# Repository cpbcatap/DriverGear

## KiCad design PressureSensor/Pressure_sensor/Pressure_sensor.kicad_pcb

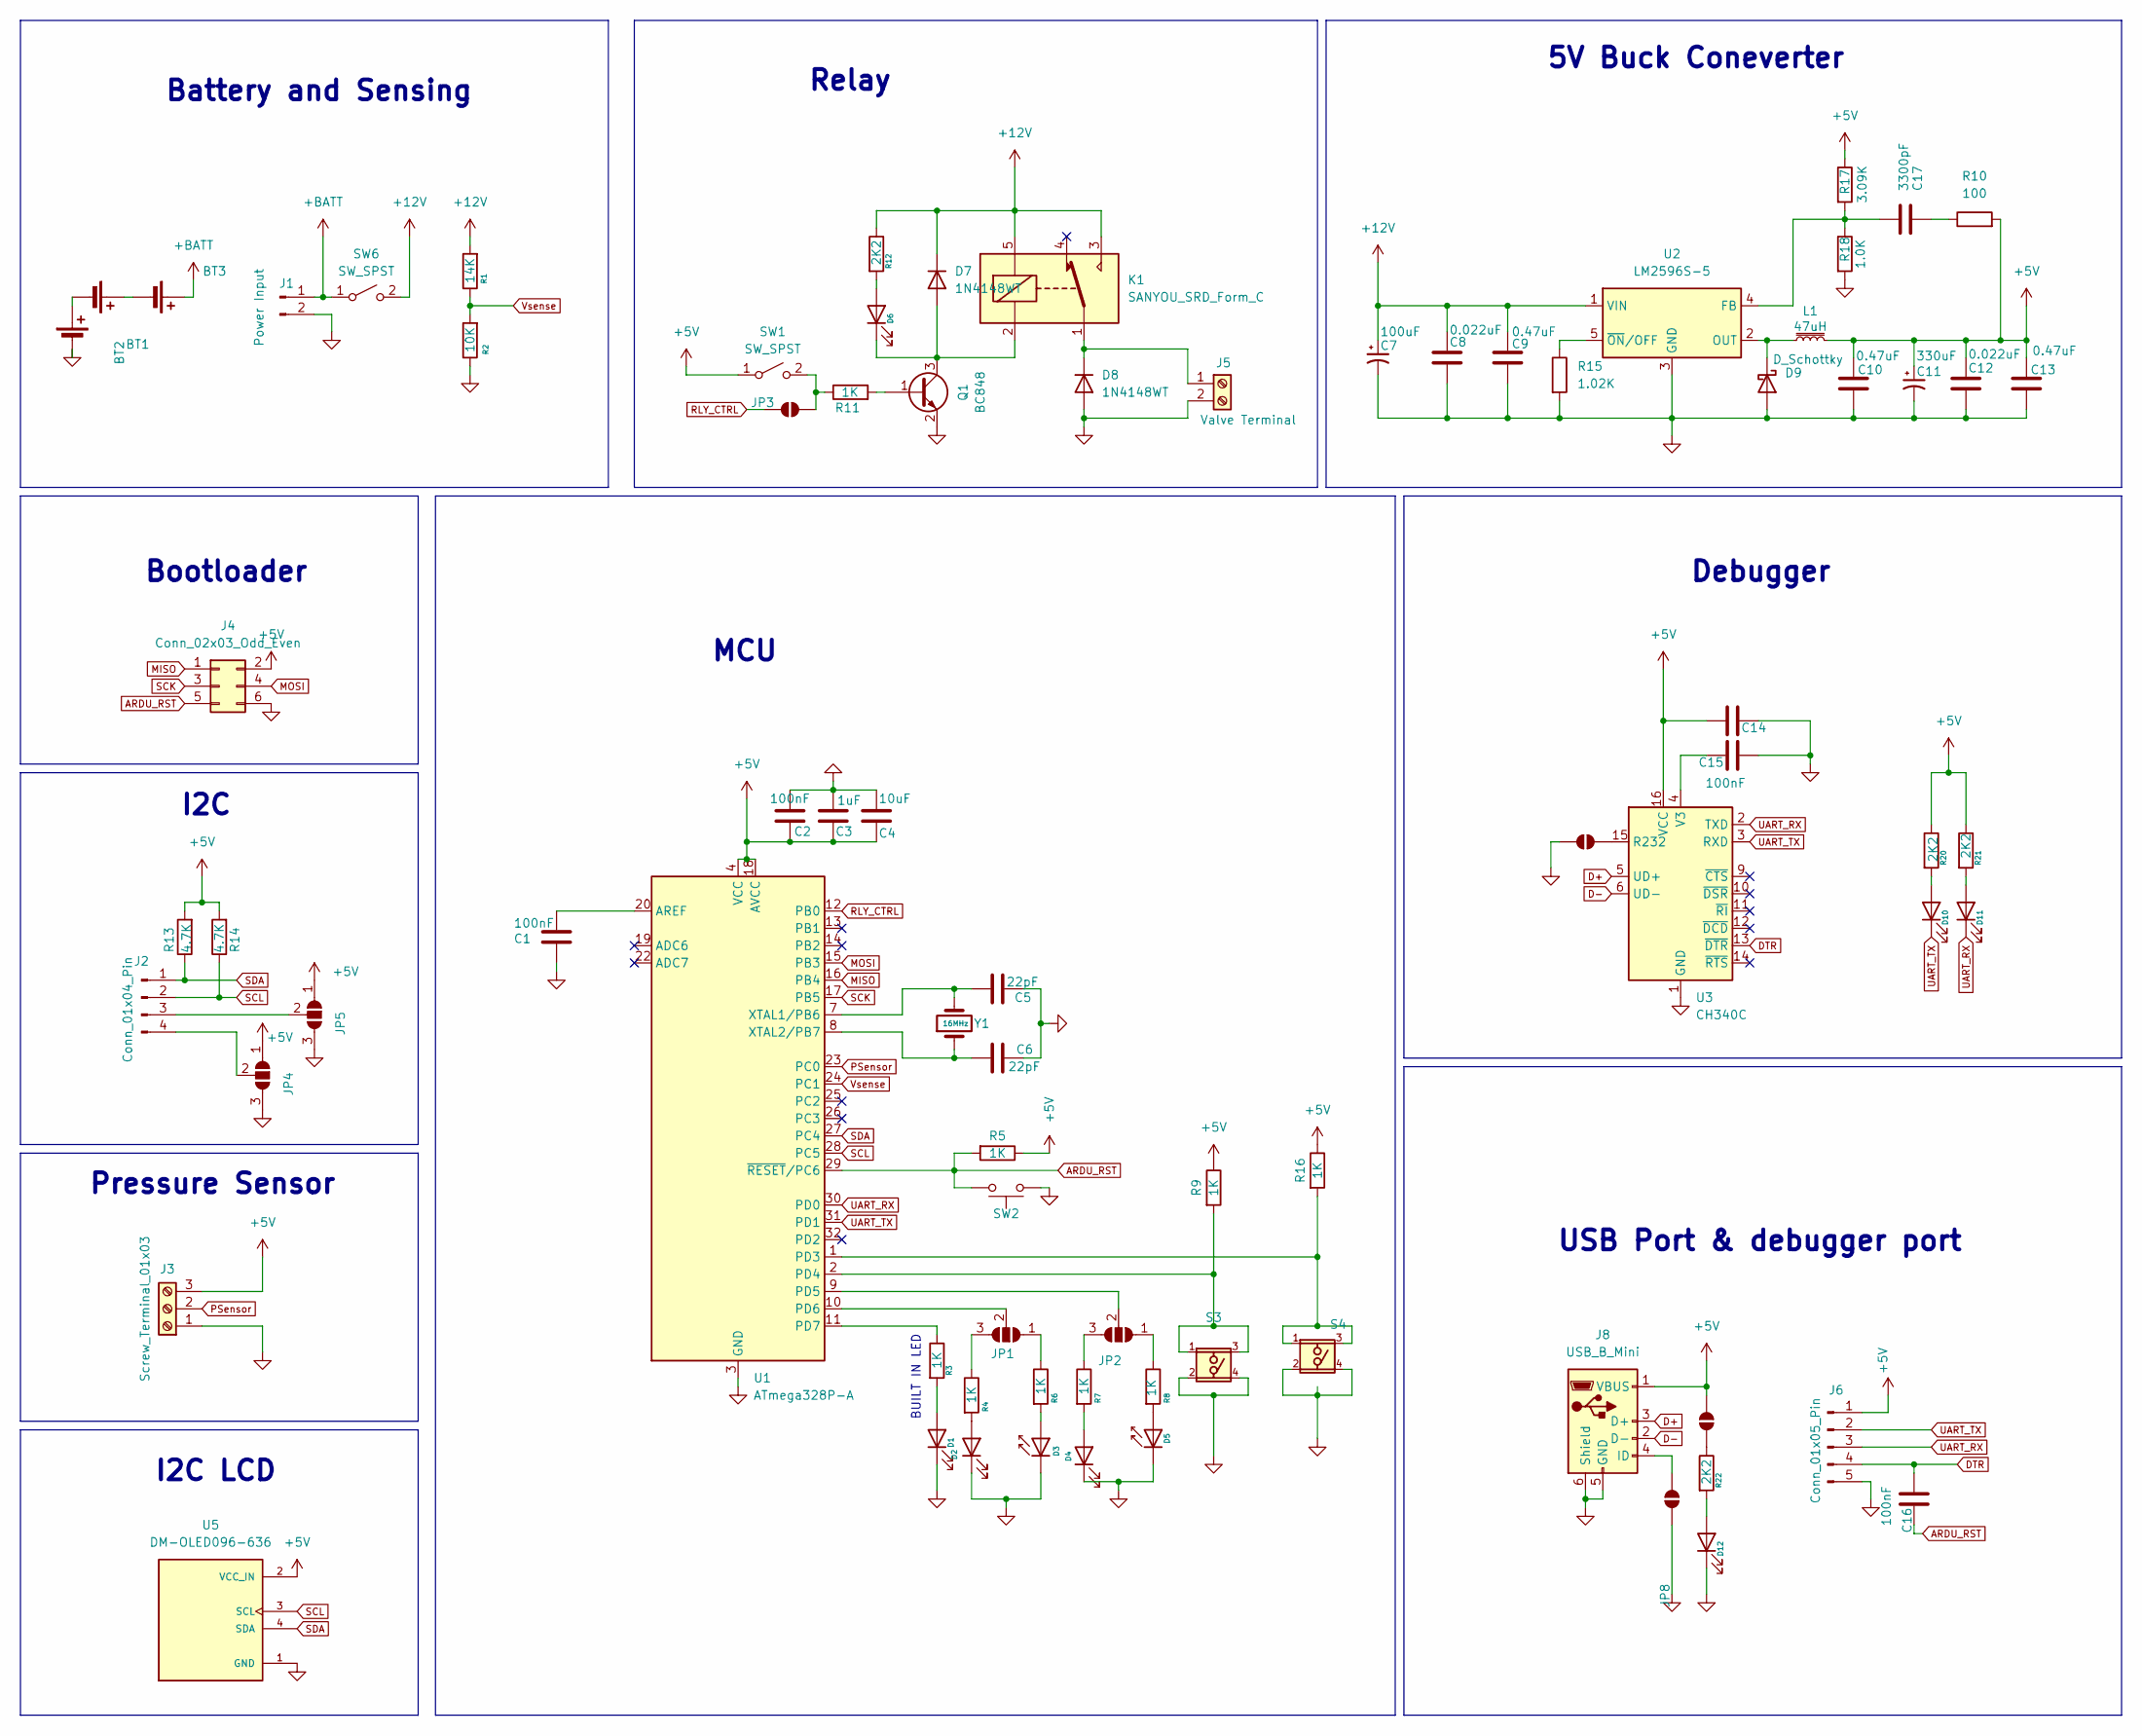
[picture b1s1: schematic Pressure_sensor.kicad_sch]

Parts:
BT1, BT2, BT3: Battery_Cell; BatteryHolder_Keystone_1042_1x18650
C1, C2, C14, C15, C16: 100nF; C_0603_1608Metric; LCSC C60474
C3: 1uF; C_0603_1608Metric; LCSC C52923
C4: 10uF; C_0603_1608Metric; LCSC C96446
C5, C6: 22pF; C_0603_1608Metric; LCSC C96446
C7: 100uF; CP_Elec_10x10.5
C8, C12: 0.022uF; C_0603_1608Metric
C9, C10, C13: 0.47uF; C_0603_1608Metric
C11: 330uF; CP_Elec_10x12.5
C17: 3300pF; C_0603_1608Metric
D1, D2, D4, D6, D10, D11, D12: LED; LED_0603_1608Metric; LCSC C2297
D3, D5: LD271; LED_D5.0mm_IRGrey
D7, D8: 1N4148WT; D_SOD-123
D9: D_Schottky; D_SMC
J1: Power Input; JST_PH_B2B-PH-K_1x02_P2.00mm_Vertical
J2: Conn_01x04_Pin; PinSocket_1x04_P2.54mm_Vertical
J3: Screw_Terminal_01x03; TerminalBlock_MaiXu_MX126-5.0-03P_1x03_P5.00mm
J4: Conn_02x03_Odd_Even; PinSocket_2x03_P2.54mm_Vertical
J5: Valve Terminal; TerminalBlock_MaiXu_MX126-5.0-02P_1x02_P5.00mm
J6: Conn_01x05_Pin; PinSocket_1x05_P2.54mm_Vertical
J8: USB_B_Mini; USB_Mini-B_Lumberg_2486_01_Horizontal
JP1, JP2, JP4, JP5: SolderJumper_3_Open; SolderJumper-3_P1.3mm_Open_RoundedPad1.0x1.5mm
JP3, JP6, JP7, JP8: SolderJumper_2_Open; SolderJumper-2_P1.3mm_Open_RoundedPad1.0x1.5mm
K1: SANYOU_SRD_Form_C; Relay_SPDT_SANYOU_SRD_Series_Form_C
L1: 47uH; L_12x12mm_H8mm
Q1: BC848; SOT-23-3
R1: 14K; R_0603_1608Metric; LCSC C23162
R2: 10K; R_0603_1608Metric; LCSC C23162
R3, R4, R5, R6, R7, R8, R9, R16: 1K; R_0603_1608Metric; LCSC C21190
R10: 100; R_0603_1608Metric
R11: 1K; R_0603_1608Metric
R12, R20, R21, R22: 2K2; R_0603_1608Metric; LCSC C21190
R13, R14: 4.7K; R_0603_1608Metric; LCSC C23162
R15: 1.02K; R_0603_1608Metric
R17: 3.09K; R_0603_1608Metric
R18: 1.0K; R_0603_1608Metric
S3, S4: TS04-66-70-BK-160-SMT; SW_TS04-66-70-BK-160-SMT; PARTREV 1.0
SW1, SW6: SW_SPST; SW_DIP_SPSTx01_Slide_9.78x4.72mm_W8.61mm_P2.54mm
SW2: SW_Push; SW_SPST_FSMSM; LCSC C2689642
U1: ATmega328P-A; TQFP-32_7x7mm_P0.8mm; LCSC C14877
U2: LM2596S-5; TO-263-5_TabPin3
U3: CH340C; SOIC-16_3.9x9.9mm_P1.27mm
U5: DM-OLED096-636; MODULE_DM-OLED096-636; PARTREV 2018-09-10
Y1: 16MHz; Crystal_HC49-4H_Vertical

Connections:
+5V: C2.2, C3.2, C4.2, C10.1, C11.1, C12.1, C13.1, C14.1, J3.3, J4.2, J6.1, J8.1 (VBUS), JP4.1 (A), JP5.1 (A), JP7.2 (B), L1.2, R5.1, R9.1, R10.2, R13.2, R14.2, R16.1, R17.1, R20.1, R21.1, SW1.1 (A), U1.4 (VCC), U1.6 (VCC), U1.18 (AVCC), U3.16 (VCC), U5.2 (VCC_IN)
+12V: C7.1, C8.1, C9.1, D7.1 (K), K1.3, K1.5, R1.2, R12.1, SW6.2 (B), U2.1 (VIN)
+BATT: BT3.1 (+), J1.1, SW6.1 (A)
ARDU_RST: C16.2, J4.5, R5.2, SW2.2, U1.29 (~RESET/PC6)
D+: J8.3 (D+), U3.5 (UD+)
D-: J8.2 (D-), U3.6 (UD-)
DTR: C16.1, J6.4, U3.13 (~DTR)
GND: BT1.2 (-), C1.2, C2.1, C3.1, C4.1, C5.2, C6.2, C7.2, C8.2, C9.2, C10.2, C11.2, C12.2, C13.2, C14.2, C15.1, D1.1 (K), D2.1 (K), D3.1 (K), D4.1 (K), D5.1 (K), D8.2 (A), D9.2 (A), D12.1 (K), J1.2, J3.1, J4.6, J5.2, J6.5, J8.5 (GND), J8.6 (Shield), JP4.3 (B), JP5.3 (B), JP6.2 (B), JP8.2 (B), Q1.2 (E), R2.1, R15.2, R18.2, S3.2, S3.4, S4.2, S4.4, SW2.1, U1.3 (GND), U1.5 (GND), U1.21 (GND), U2.3 (GND), U3.1 (GND), U5.1 (GND), U5.S1, U5.S2, U5.S3, U5.S4
MISO: J4.1, U1.16 (PB4)
MOSI: J4.4, U1.15 (PB3)
unnamed: BT1.1 (+), BT2.2 (-)
unnamed: BT2.1 (+), BT3.2 (-)
unnamed: C17.2, R10.1
unnamed: D1.2 (A), R3.2
unnamed: D2.2 (A), R4.2
unnamed: D3.2 (A), R6.2
unnamed: D4.2 (A), R7.2
unnamed: D5.2 (A), R8.2
unnamed: D6.2 (A), R12.2
unnamed: D6.1 (K), D7.2 (A), K1.2, Q1.3 (C)
unnamed: D8.1 (K), J5.1, K1.1
unnamed: D9.1 (K), L1.1, U2.2 (OUT)
unnamed: D10.2 (A), R20.2
unnamed: D11.2 (A), R21.2
unnamed: D12.2 (A), R22.2
unnamed: J2.3, JP5.2 (C)
unnamed: J2.4, JP4.2 (C)
unnamed: J8.4 (ID), JP8.1 (A)
unnamed: JP1.1 (A), R6.1
unnamed: JP1.3 (B), R4.1
unnamed: JP1.2 (C), U1.10 (PD6)
unnamed: JP2.1 (A), R8.1
unnamed: JP2.3 (B), R7.1
unnamed: JP2.2 (C), U1.9 (PD5)
unnamed: JP3.1 (A), R11.1, SW1.2 (B)
unnamed: JP6.1 (A), U3.15 (R232)
unnamed: JP7.1 (A), R22.1
unnamed: Q1.1 (B), R11.2
unnamed: C1.1, U1.20 (AREF)
unnamed: R16.2, S4.1, S4.3, U1.1 (PD3)
unnamed: R9.2, S3.1, S3.3, U1.2 (PD4)
unnamed: R3.1, U1.11 (PD7)
unnamed: C5.1, U1.7 (XTAL1/PB6), Y1.2
unnamed: C6.1, U1.8 (XTAL2/PB7), Y1.1
unnamed: C17.1, R17.2, R18.1, U2.4 (FB)
unnamed: R15.1, U2.5 (~ON/OFF)
unnamed: C15.2, U3.4 (V3)
PSensor: J3.2, U1.23 (PC0)
RLY_CTRL: JP3.2 (B), U1.12 (PB0)
SCK: J4.3, U1.17 (PB5)
SCL: J2.2, R14.1, U1.28 (PC5), U5.3 (SCL)
SDA: J2.1, R13.1, U1.27 (PC4), U5.4 (SDA)
UART_RX: D11.1 (K), J6.3, U1.30 (PD0), U3.2 (TXD)
UART_TX: D10.1 (K), J6.2, U1.31 (PD1), U3.3 (RXD)
Vsense: R1.1, R2.2, U1.24 (PC1)

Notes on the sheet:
Battery and Sensing
USB Port & debugger port
Pressure Sensor
MCU
I2C LCD
Debugger
5V Buck Coneverter
Bootloader
BUILT IN LED
Relay
I2C

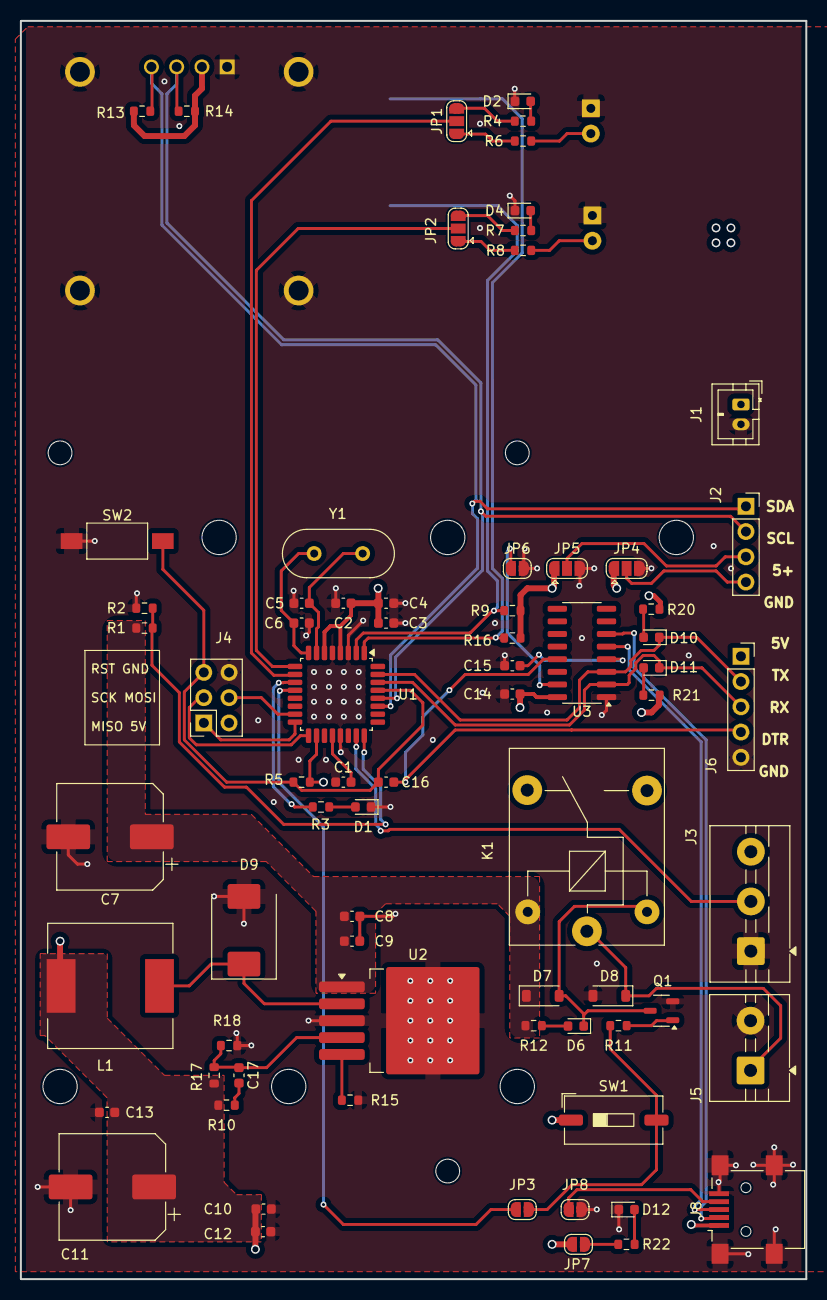
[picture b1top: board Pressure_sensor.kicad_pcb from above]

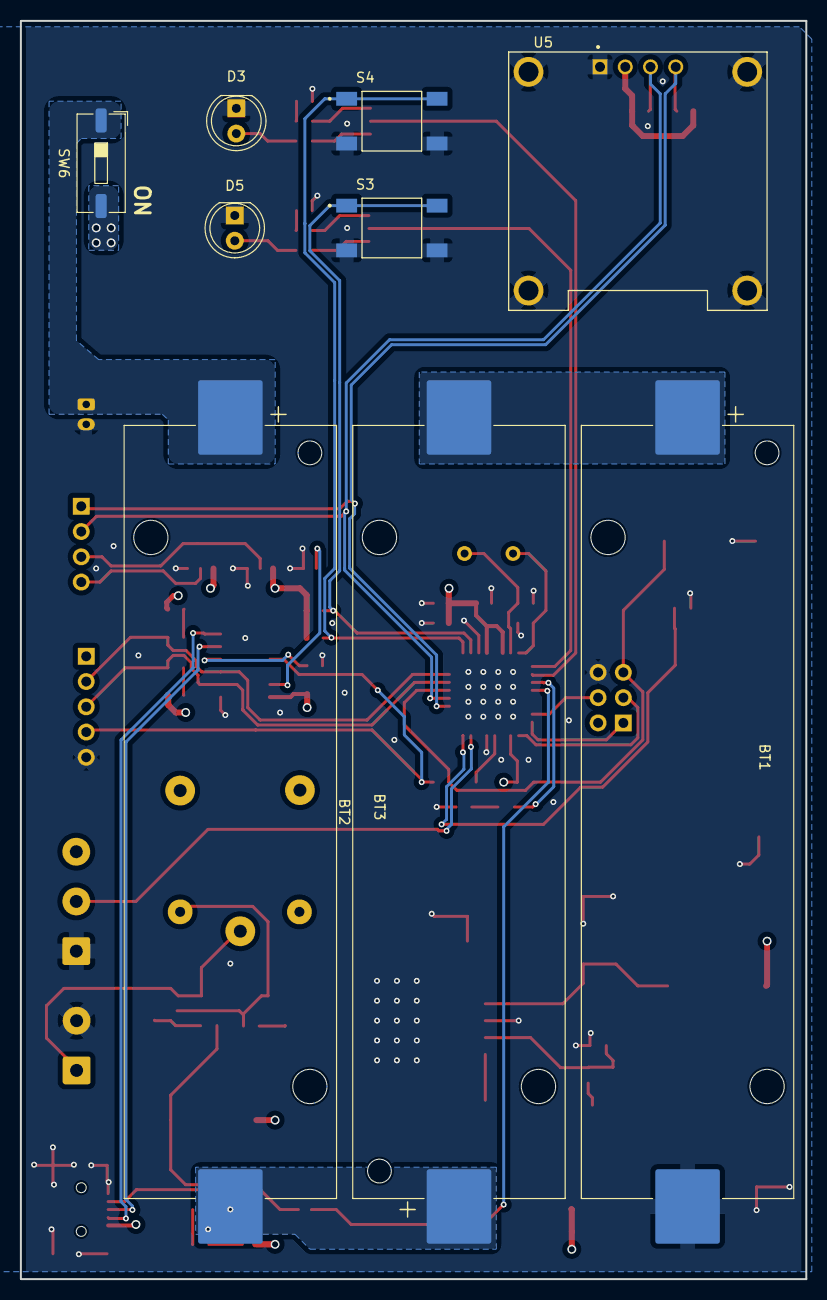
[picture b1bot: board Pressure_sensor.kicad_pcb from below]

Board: 4 copper layers, 79.0 x 126.6 mm, 81 parts (9 on the bottom side), 55 nets.

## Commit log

2025-08-13 Add PressureSensor files
2025-08-13 Add Pressure_sensor KiCad files
2025-08-14 push
2025-08-14 push
    1. Battery 2p1a to 3S
    2. Relay Switch - pull down to pull up
    3. Scratch - Inserted true OLED display
2025-08-14 Push
    1. Ensured 3D file are locale at the project file
    2. completed 3D
2025-08-26 For Checking
    - Data tracks
    - Components placement
    do not mind the ff will do after this checking:
    - power tracks - zoning
    - zone layer
2025-08-26 Habol lang
2025-09-05 initial checking for final placement
    For checking
    1. tracks std
    2. zones
    3. layering
    4, placement
    5. ERC std
2025-09-05 Reviewed by Nes
    DONE
    1. each GND pad have via
    2. heatsink for U2 and ATMEGA
    for clarification
    1. added mounting holes
    2. added silk for jumper wires?
